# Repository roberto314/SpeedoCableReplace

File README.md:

# SpeedoCableReplace
An electronic replacement for a Speedometer Cable from an old car.

This is a simple solution for a broken speedometer cable. 
It uses a sensor on the wheels or on the propshaft and converts
it to a PWM for a small BLDC Motor.
I found some on ebay. They look like this:

This motor should be mounted to the speedometer. The microcontroller is a STM32F103 
maple mini board. The firmware is based on ChibiOS 20 (trunk).

Schematic:

[Schematic](schematics/pdf/Tachoconverter.pdf)

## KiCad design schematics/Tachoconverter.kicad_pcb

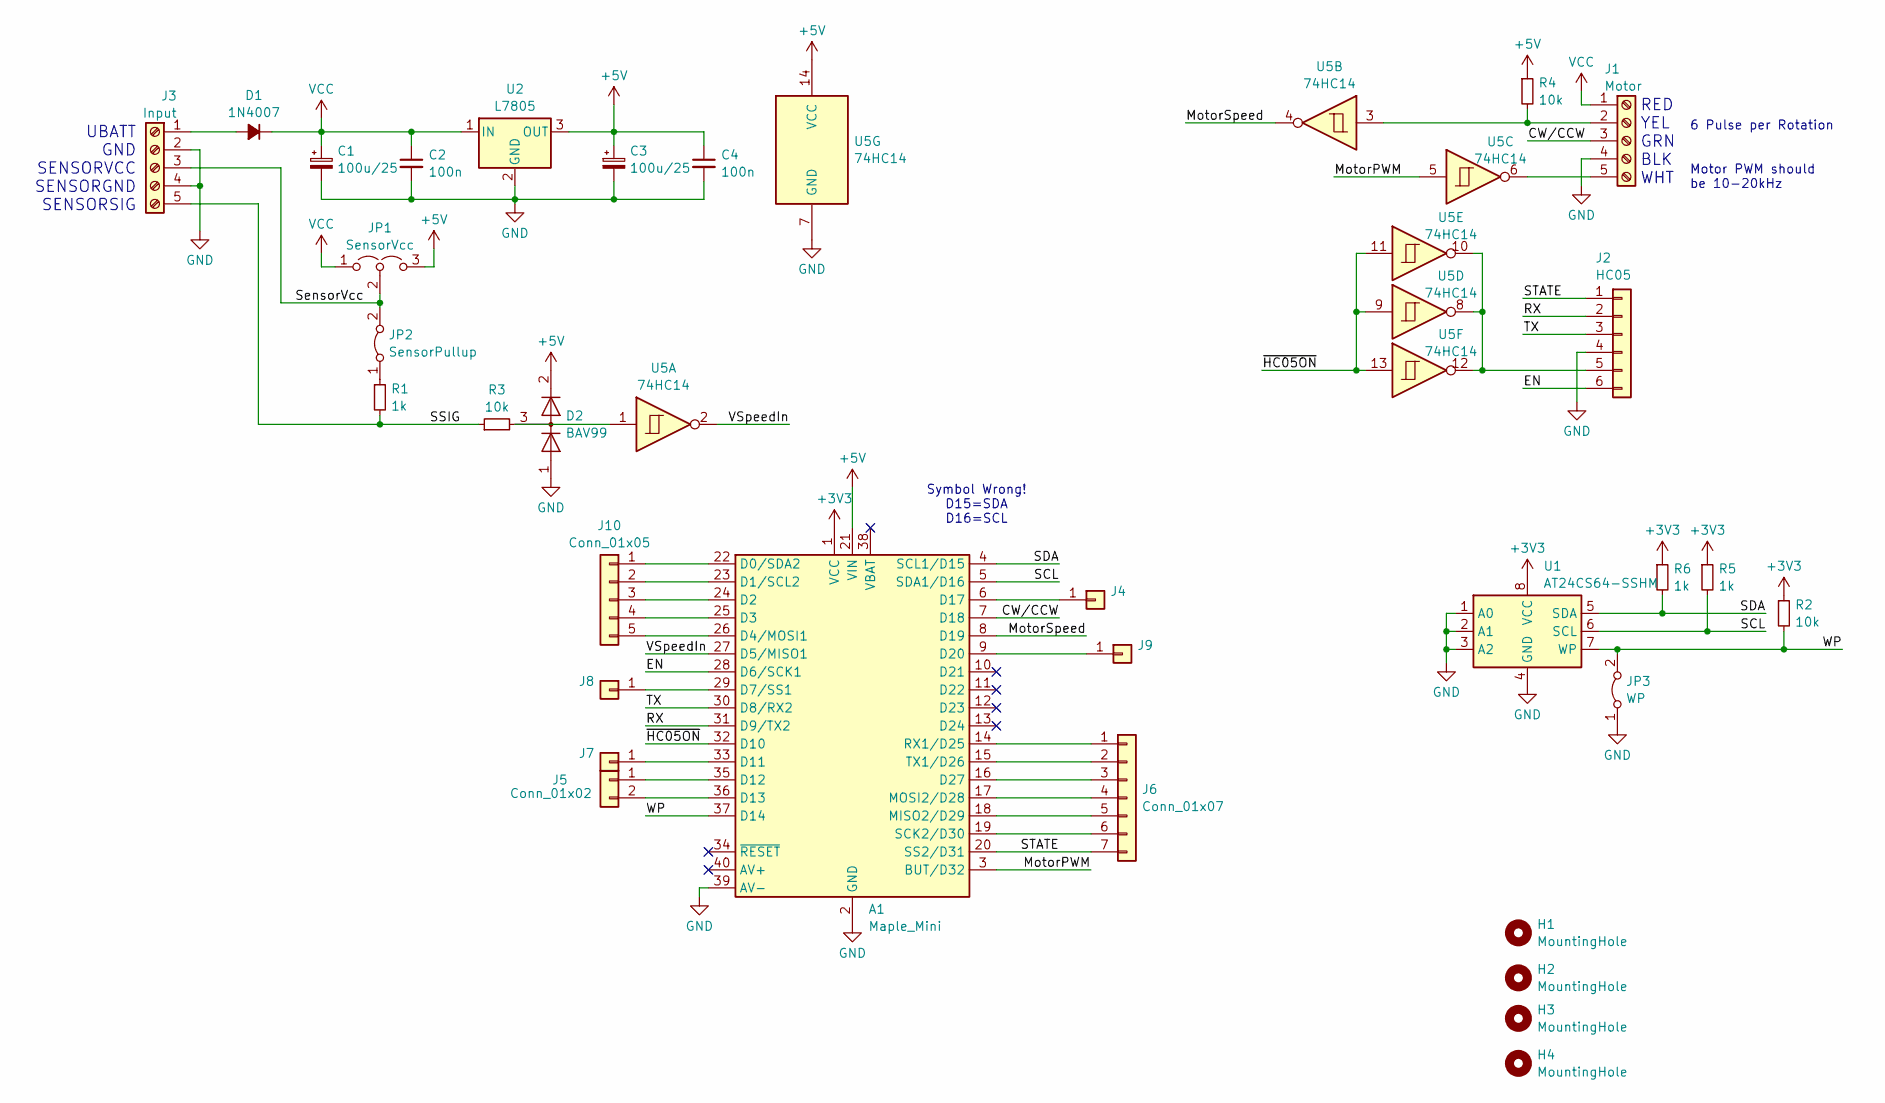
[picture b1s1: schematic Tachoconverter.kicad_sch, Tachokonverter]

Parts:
A1: Maple_Mini
C1, C3: 100u/25; CP_EIA-7343-31_Kemet-D
C2, C4: 100n; C_1206_3216Metric_Pad1.33x1.80mm_HandSolder
D1: 1N4007; D_SMA
D2: BAV99; SOT-23_Handsoldering
H1, H2, H3, H4: MountingHole; MountingHole_3.2mm_M3
J1: Motor; TerminalBlock_MetzConnect_Type094_RT03505HBLU_1x05_P5.00mm_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
J2: HC05; PinHeader_1x06_P2.54mm_Vertical
J3: Input; TerminalBlock_MetzConnect_Type094_RT03505HBLU_1x05_P5.00mm_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
J4, J7, J8, J9: Conn_01x01; PinHeader_1x01_P2.54mm_Vertical
J5: Conn_01x02; PinHeader_1x02_P2.54mm_Vertical
J6: Conn_01x07; PinHeader_1x07_P2.54mm_Vertical
J10: Conn_01x05; PinHeader_1x05_P2.54mm_Vertical
JP1: SensorVcc; PinHeader_1x03_P2.54mm_Vertical
JP2: SensorPullup; SolderJumper-2_P1.3mm_Bridged_RoundedPad1.0x1.5mm
JP3: WP; SolderJumper-2_P1.3mm_Bridged_RoundedPad1.0x1.5mm
R1, R5, R6: 1k; R_1206_3216Metric_Pad1.30x1.75mm_HandSolder
R2, R3, R4: 10k; R_1206_3216Metric_Pad1.30x1.75mm_HandSolder
U1: AT24CS64-SSHM; DIP-8_W7.62mm_Socket_LongPads
U2: L7805; TO-220-3_Vertical
U5: 74HC14; SOIC-14_3.9x8.7mm_P1.27mm

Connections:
+3V3: A1.1 (VCC), R2.1, R5.1, R6.1, U1.8 (VCC)
+5V: A1.21 (VIN), C3.1, C4.1, D2.2 (A), JP1.3 (B), R4.1, U2.3 (OUT), U5.14 (VCC)
/CW/CCW: A1.7 (D18), J1.3
/EN: A1.28 (D6/SCK1), J2.6
/MotorPWM: A1.3 (BUT/D32), U5.5
/MotorSpeed: A1.8 (D19), U5.4
/RX: A1.31 (D9/TX2), J2.2
/SCL: A1.5 (SDA1/D16), R5.2, U1.6 (SCL)
/SDA: A1.4 (SCL1/D15), R6.2, U1.5 (SDA)
/SSIG: J3.5, R1.2, R3.1
/STATE: A1.20 (SS2/D31), J2.1, J6.7
/SensorVcc: J3.3, JP1.2 (C), JP2.2 (B)
/TX: A1.30 (D8/RX2), J2.3
/VSpeedIn: A1.27 (D5/MISO1), U5.2
/WP: A1.37 (D14), JP3.2 (B), R2.2, U1.7 (WP)
/~HC05ON: A1.32 (D10), U5.9, U5.11, U5.13
GND: A1.2 (GND), A1.39 (AV-), C1.2, C2.2, C3.2, C4.2, D2.1 (K), J1.4, J2.4, J3.2, J3.4, JP3.1 (A), U1.1 (A0), U1.2 (A1), U1.3 (A2), U1.4 (GND), U2.2 (GND), U5.7 (GND)
unnamed: A1.22 (D0/SDA2), J10.1
unnamed: A1.23 (D1/SCL2), J10.2
unnamed: A1.24 (D2), J10.3
unnamed: A1.25 (D3), J10.4
unnamed: A1.26 (D4/MOSI1), J10.5
unnamed: A1.29 (D7/SS1), J8.1
unnamed: A1.33 (D11), J7.1
unnamed: A1.35 (D12), J5.1
unnamed: A1.36 (D13), J5.2
unnamed: A1.6 (D17), J4.1
unnamed: A1.9 (D20), J9.1
unnamed: A1.16 (D27), J6.3
unnamed: A1.18 (MISO2/D29), J6.5
unnamed: A1.17 (MOSI2/D28), J6.4
unnamed: A1.14 (RX1/D25), J6.1
unnamed: A1.19 (SCK2/D30), J6.6
unnamed: A1.15 (TX1/D26), J6.2
unnamed: D1.2 (A), J3.1
unnamed: D2.3 (K), R3.2, U5.1
unnamed: J1.2, R4.2, U5.3
unnamed: J1.5, U5.6
unnamed: J2.5, U5.8, U5.10, U5.12
unnamed: JP2.1 (A), R1.1
VCC: C1.1, C2.1, D1.1 (K), J1.1, JP1.1 (A), U2.1 (IN)

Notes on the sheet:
Symbol Wrong! D15=SDA D16=SCL
RED YEL GRN BLK WHT
6 Pulse per Rotation
Motor PWM should be 10-20kHz
UBATT GND SENSORVCC SENSORGND SENSORSIG

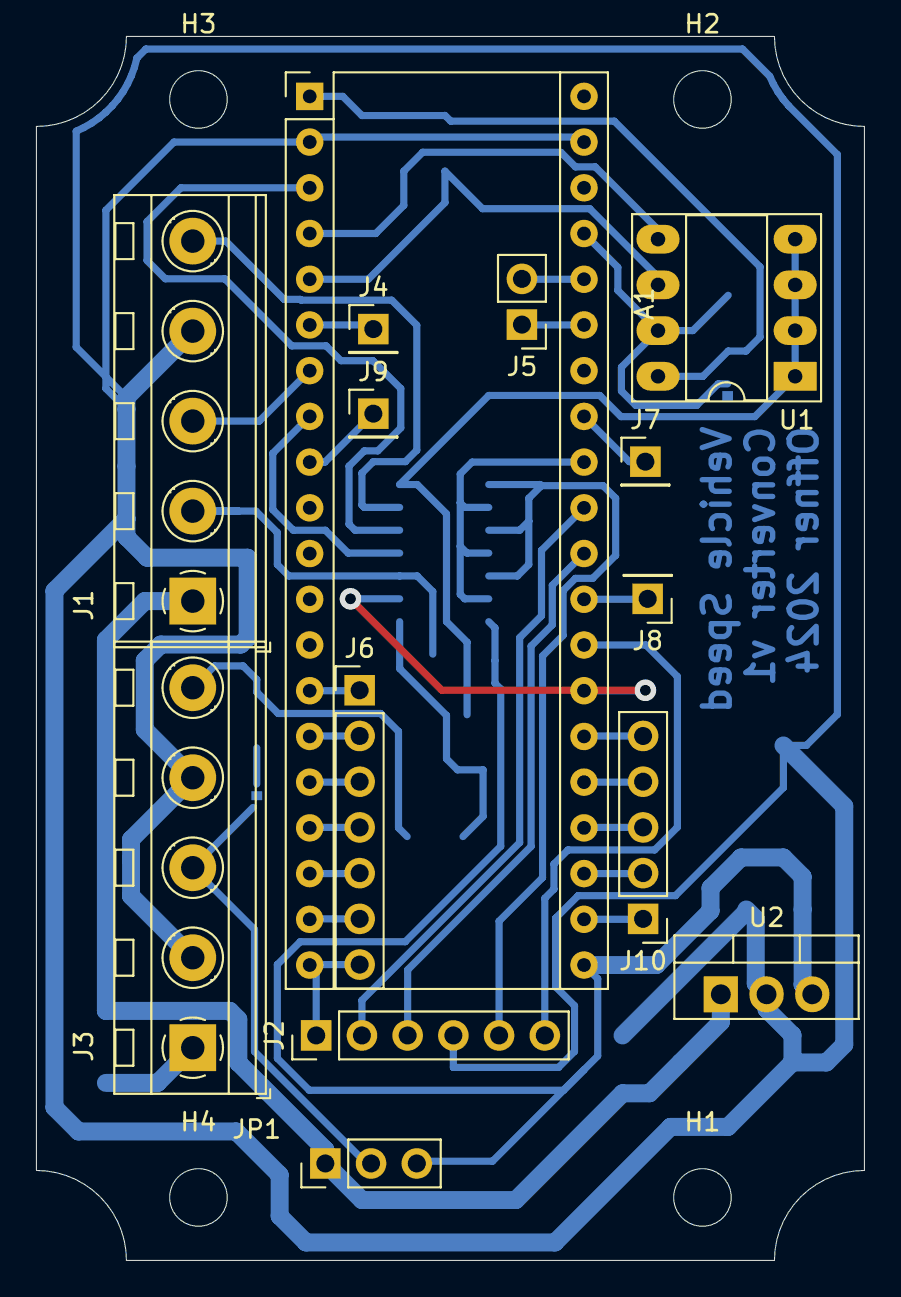
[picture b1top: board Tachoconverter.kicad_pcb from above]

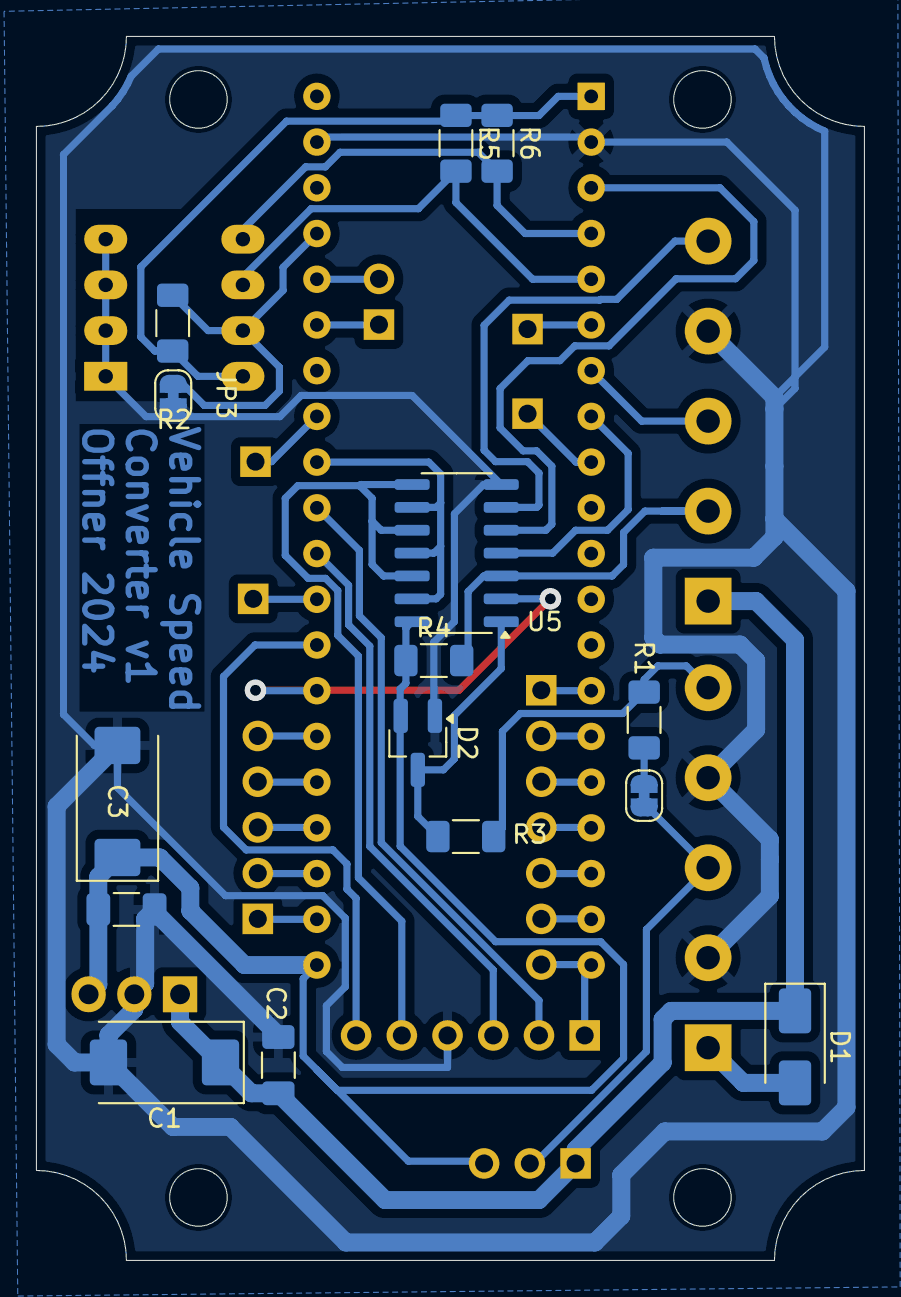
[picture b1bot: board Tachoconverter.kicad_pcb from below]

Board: 2 copper layers, 46.0 x 68.0 mm, 33 parts (15 on the bottom side), 41 nets.

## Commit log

2024-04-25 Initial
2024-04-25 board changed
2024-05-22 schematic update
2024-05-22 Readme update
2024-05-22 Firmware update
2024-06-22 code progress
